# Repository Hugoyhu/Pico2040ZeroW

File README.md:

# Pico2040ZeroW
Raspberry Pi Form Factor, RP2040, Wireless support with ESP-01

2 Layer board, Rpi Form factor for pwr in, SD, pinout.

Optional ESP01 for wifi connectivity.

NOTE: THIS IS A NON-TESTED DESIGN. I HAVE NOT YET TRIED IT NOR REVIEWED WITH OTHERS. PLEASE KEEP THIS IN MIND WHEN TRYING TO BUILD ONE YOURSELF.

It is compatible with Python, (snek lang), C/C++, and Rust.

Schematic is modified off the Raspberry Pi foundation's reference schematic and carrier demo board schematics with modifications.

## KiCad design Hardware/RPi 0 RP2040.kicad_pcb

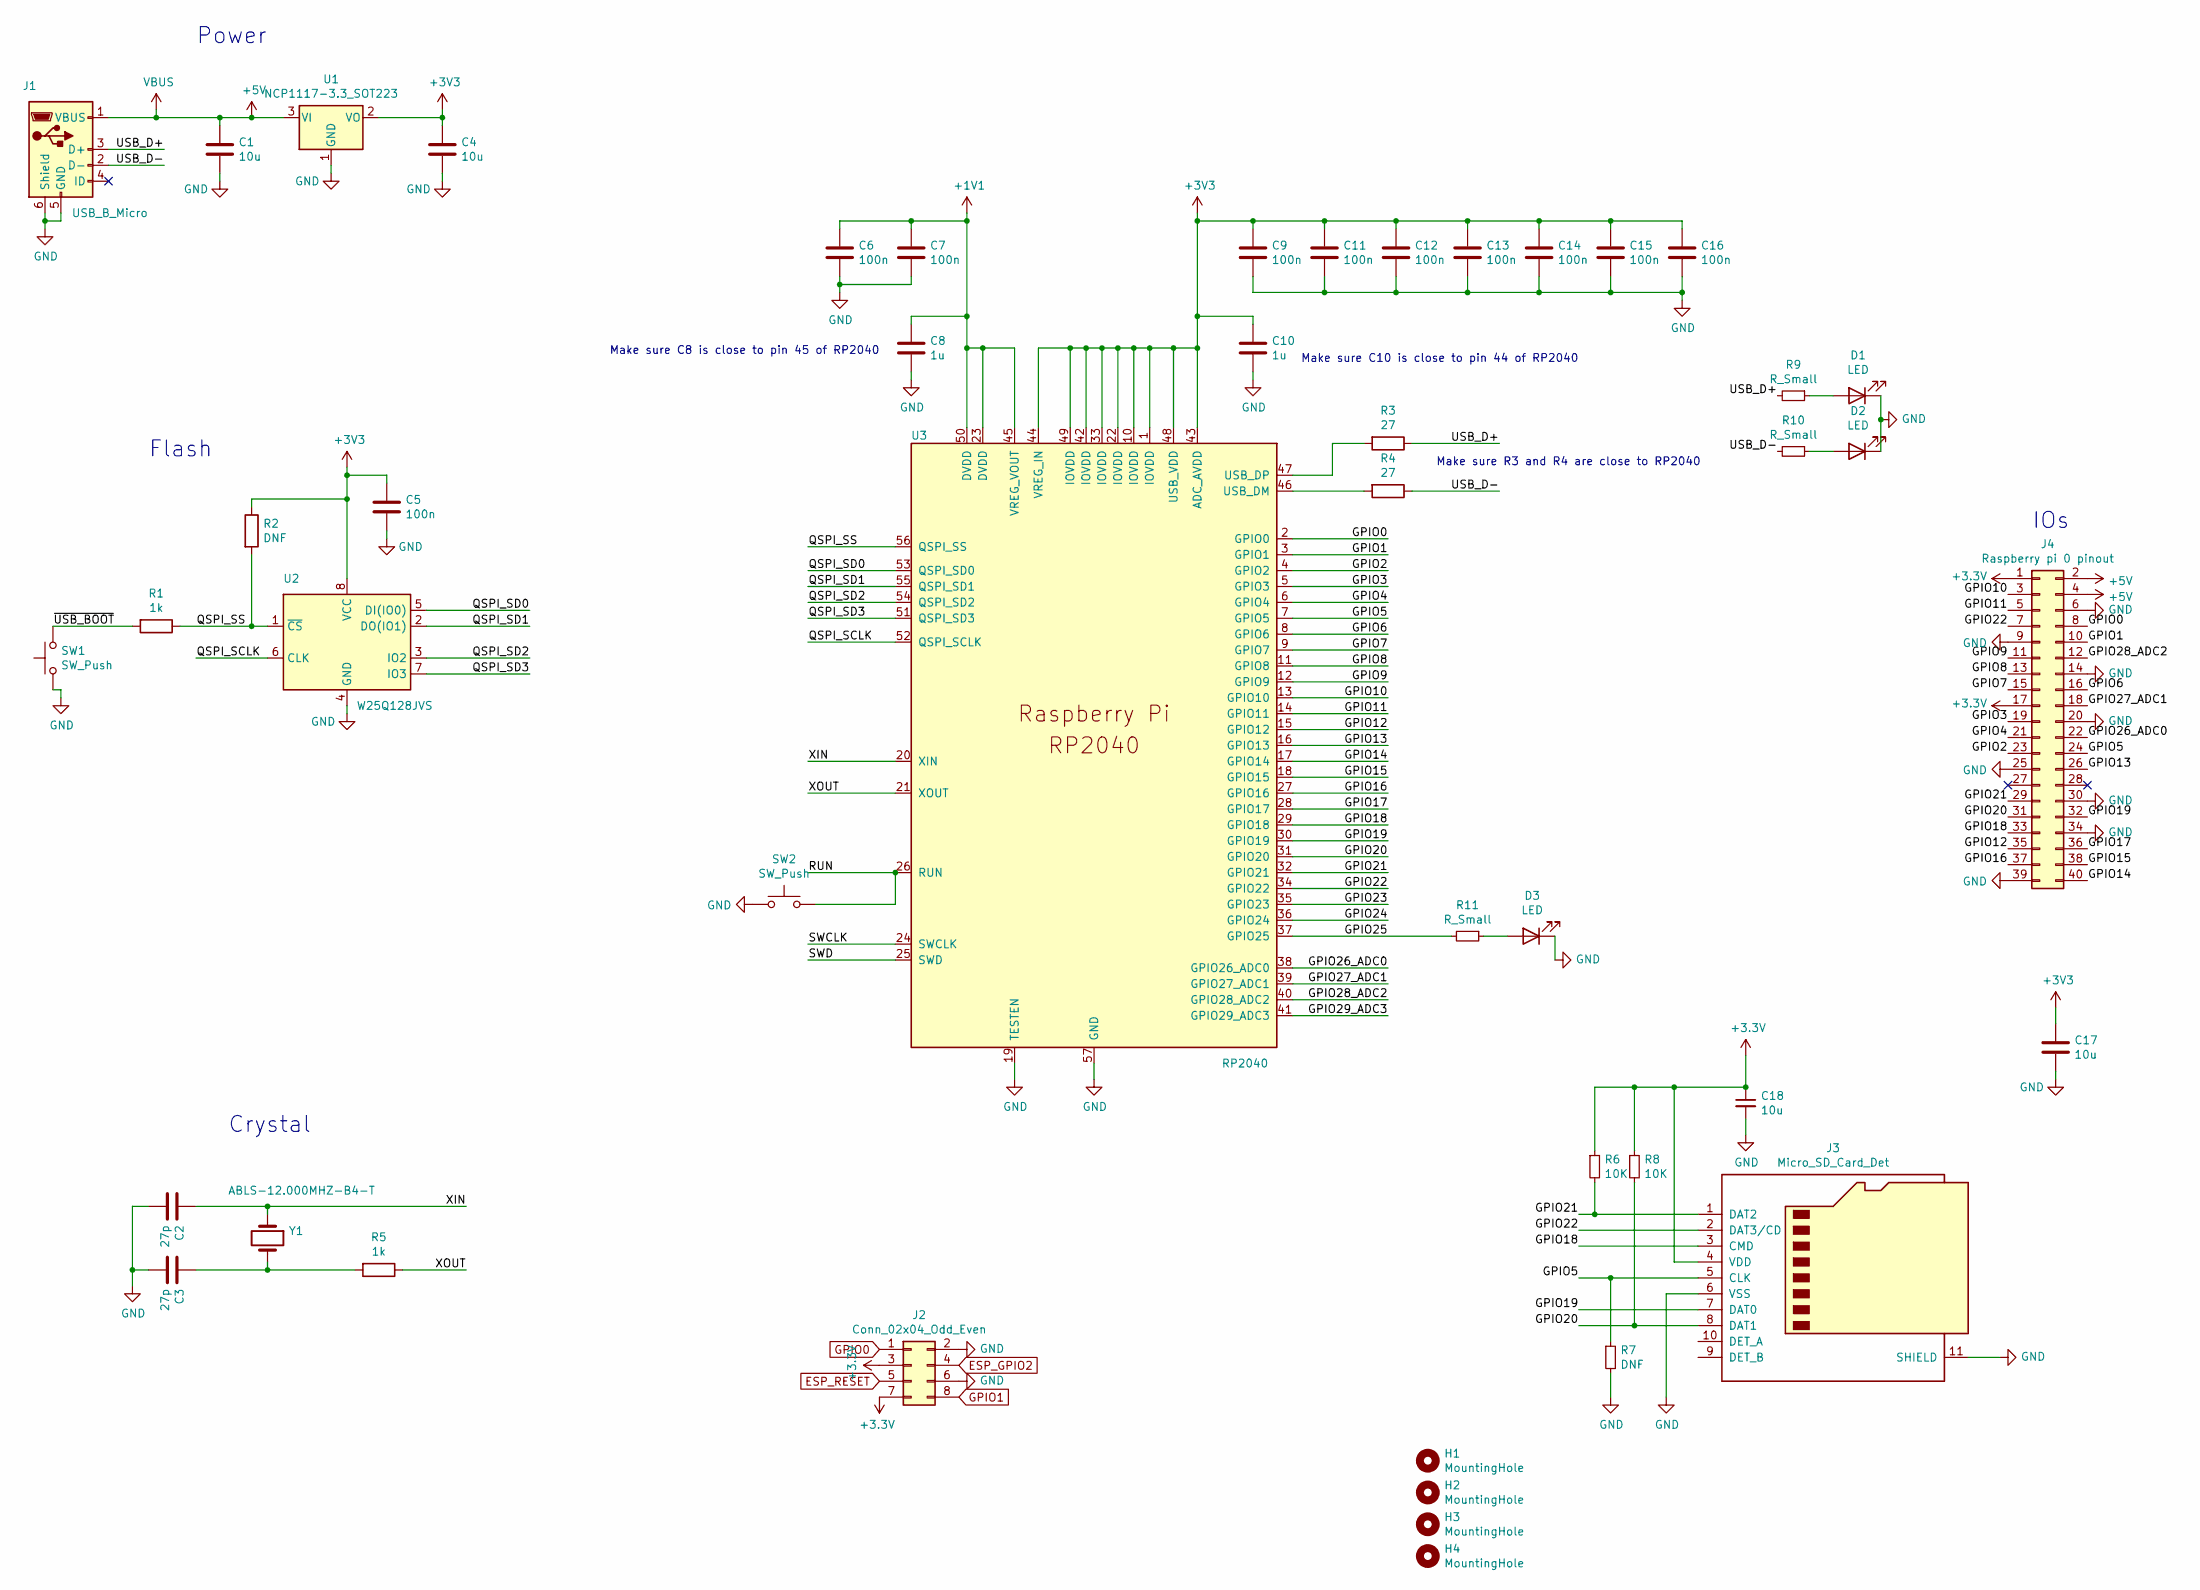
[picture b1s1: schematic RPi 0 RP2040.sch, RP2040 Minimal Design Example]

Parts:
C1, C4, C17, C18: 10u; C_0805_2012Metric_Pad1.18x1.45mm_HandSolder
C2, C3: 27p; C_0603_1608Metric_Pad1.08x0.95mm_HandSolder
C5, C6, C7, C9, C11, C12, C13, C14, C15, C16: 100n; C_0603_1608Metric_Pad1.08x0.95mm_HandSolder
C8, C10: 1u; C_0603_1608Metric_Pad1.08x0.95mm_HandSolder
D1, D2, D3: LED; LED_0603_1608Metric_Pad1.05x0.95mm_HandSolder
H1, H2, H3, H4: MountingHole; MountingHole_2.7mm_M2.5
J1: USB_B_Micro; USB_Micro-B_Amphenol_10103594-0001LF_Horizontal_modified
J2: Conn_02x04_Odd_Even; PinSocket_2x04_P2.54mm_Vertical
J3: Micro_SD_Card_Det; 104031-0811
J4: Raspberry pi 0 pinout; PinSocket_2x20_P2.54mm_Vertical
R1, R5: 1k; R_0603_1608Metric_Pad0.98x0.95mm_HandSolder
R2, R7: DNF; R_0603_1608Metric_Pad0.98x0.95mm_HandSolder
R3, R4: 27; R_0603_1608Metric_Pad0.98x0.95mm_HandSolder
R6, R8: 10K; R_0603_1608Metric_Pad0.98x0.95mm_HandSolder
R9, R10, R11: R_Small; R_0603_1608Metric_Pad0.98x0.95mm_HandSolder
SW1, SW2: SW_Push; Panasonic_EVQPUK_EVQPUB
U1: NCP1117-3.3_SOT223; SOT-223-3_TabPin2
U2: W25Q128JVS; SOIC-8_5.23x5.23mm_P1.27mm
U3: RP2040; RP2040-QFN-56
Y1: ABLS-12.000MHZ-B4-T; Crystal_SMD_HC49-US

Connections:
+1V1: C6.1, C7.1, C8.1, U3.23 (DVDD), U3.45 (VREG_VOUT), U3.50 (DVDD)
+5V: C1.1, J1.1 (VBUS), J4.2, J4.4, U1.3 (VI)
/GPIO2: J4.23, U3.4 (GPIO2)
/GPIO3: J4.19, U3.5 (GPIO3)
/GPIO4: J4.21, U3.6 (GPIO4)
/GPIO5: J3.5 (CLK), J4.24, R7.1, U3.7 (GPIO5)
/GPIO6: J4.16, U3.8 (GPIO6)
/GPIO7: J4.15, U3.9 (GPIO7)
/GPIO8: J4.13, U3.11 (GPIO8)
/GPIO9: J4.11, U3.12 (GPIO9)
/GPIO10: J4.3, U3.13 (GPIO10)
/GPIO11: J4.5, U3.14 (GPIO11)
/GPIO12: J4.35, U3.15 (GPIO12)
/GPIO13: J4.26, U3.16 (GPIO13)
/GPIO14: J4.40, U3.17 (GPIO14)
/GPIO15: J4.38, U3.18 (GPIO15)
/GPIO16: J4.37, U3.27 (GPIO16)
/GPIO17: J4.36, U3.28 (GPIO17)
/GPIO18: J3.3 (CMD), J4.33, U3.29 (GPIO18)
/GPIO19: J3.7 (DAT0), J4.32, U3.30 (GPIO19)
/GPIO20: J3.8 (DAT1), J4.31, R8.2, U3.31 (GPIO20)
/GPIO21: J3.1 (DAT2), J4.29, R6.2, U3.32 (GPIO21)
/GPIO22: J3.2 (DAT3/CD), J4.7, U3.34 (GPIO22)
/GPIO23: U3.35 (GPIO23)
/GPIO24: U3.36 (GPIO24)
/GPIO25: R11.2, U3.37 (GPIO25)
/GPIO26_ADC0: J4.22, U3.38 (GPIO26_ADC0)
/GPIO27_ADC1: J4.18, U3.39 (GPIO27_ADC1)
/GPIO28_ADC2: J4.12, U3.40 (GPIO28_ADC2)
/GPIO29_ADC3: U3.41 (GPIO29_ADC3)
/QSPI_SCLK: U2.6 (CLK), U3.52 (QSPI_SCLK)
/QSPI_SD0: U2.5 (DI(IO0)), U3.53 (QSPI_SD0)
/QSPI_SD1: U2.2 (DO(IO1)), U3.55 (QSPI_SD1)
/QSPI_SD2: U2.3 (IO2), U3.54 (QSPI_SD2)
/QSPI_SD3: U2.7 (IO3), U3.51 (QSPI_SD3)
/QSPI_SS: R1.1, R2.2, U2.1 (~CS), U3.56 (QSPI_SS)
/RUN: SW2.2, U3.26 (RUN)
/SWCLK: U3.24 (SWCLK)
/SWD: U3.25 (SWD)
/USB_D+: J1.3 (D+), R3.1, R9.2
/USB_D-: J1.2 (D-), R4.1, R10.2
/XIN: C2.1, U3.20 (XIN), Y1.1
/XOUT: R5.1, U3.21 (XOUT)
/~USB_BOOT: R1.2, SW1.2
ESP_GPIO2: J2.4
ESP_RESET: J2.5
GND: C1.2, C2.2, C3.2, C4.2, C5.2, C6.2, C7.2, C8.2, C9.2, C10.2, C11.2, C12.2, C13.2, C14.2, C15.2, C16.2, C17.2, C18.2, D1.1 (K), D2.1 (K), D3.1 (K), J1.5 (GND), J1.6 (Shield), J2.2, J2.6, J3.6 (VSS), J3.11 (SHIELD), J4.6, J4.9, J4.14, J4.20, J4.25, J4.30, J4.34, J4.39, R7.2, SW1.1, SW2.1, U1.1 (GND), U2.4 (GND), U3.19 (TESTEN), U3.57 (GND)
GPIO0: J2.1, J4.8, U3.2 (GPIO0)
GPIO1: J2.8, J4.10, U3.3 (GPIO1)
unnamed: C3.1, R5.2, Y1.2
unnamed: D1.2 (A), R9.1
unnamed: D2.2 (A), R10.1
unnamed: D3.2 (A), R11.1
unnamed: R3.2, U3.47 (USB_DP)
unnamed: R4.2, U3.46 (USB_DM)

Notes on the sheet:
Make sure C10 is close to pin 44 of RP2040
Make sure C8 is close to pin 45 of RP2040
Crystal
Flash
Power
IOs
Make sure R3 and R4 are close to RP2040

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
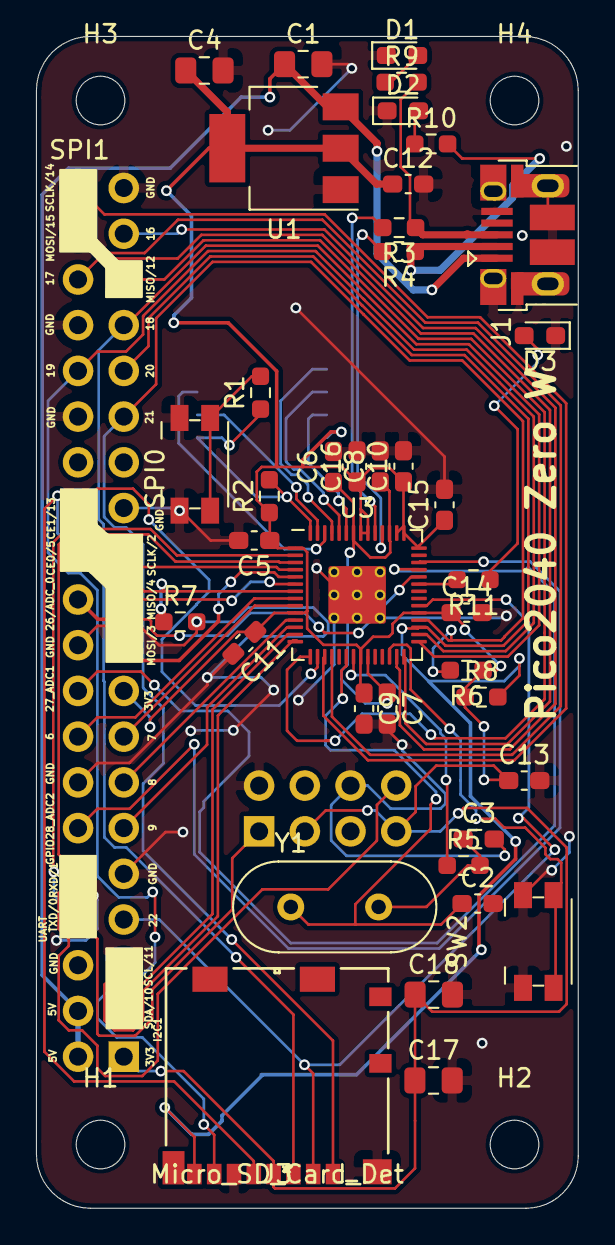
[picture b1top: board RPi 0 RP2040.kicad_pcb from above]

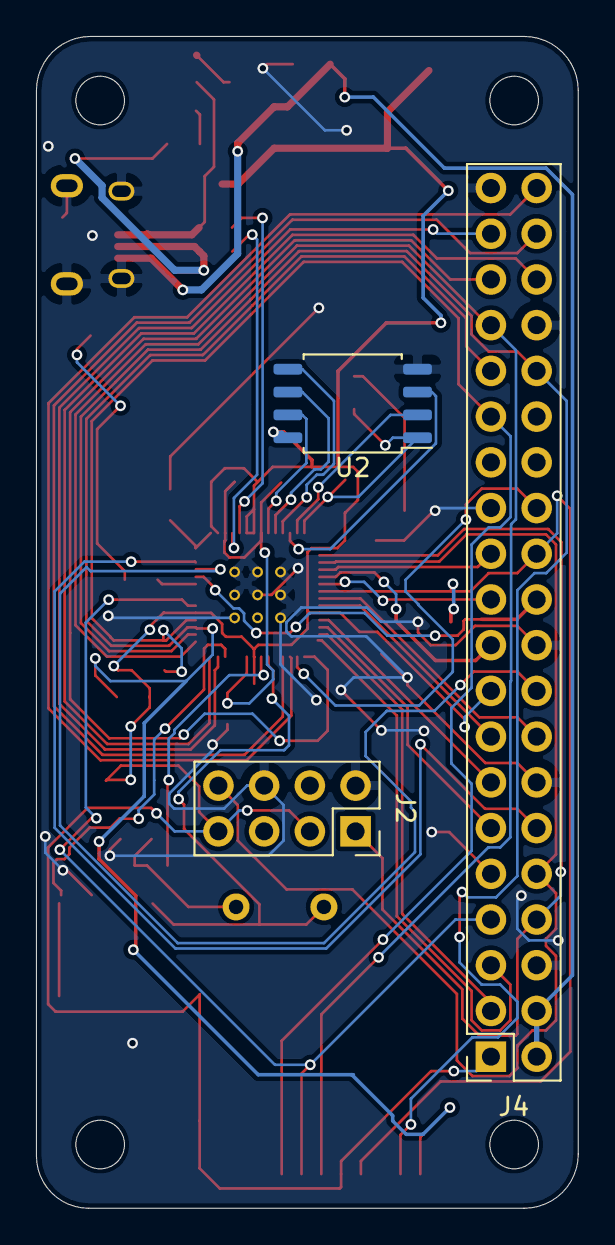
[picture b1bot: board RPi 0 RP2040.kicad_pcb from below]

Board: 2 copper layers, 30.1 x 65.1 mm, 46 parts (3 on the bottom side), 49 nets.

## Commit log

2021-02-10 Add hardware files
2021-02-12 Create v1.1 Folder and Info Txt file
2021-02-12 Add files via upload
    Add PCB design files
2021-02-12 Add files via upload
    Add images of PCB and Schematic
2021-02-12 Add Images of PCB + Schematic, rename
2021-02-12 Upload PCB Render
2021-02-12 [ImgBot] Optimize images
    *Total -- 1,136.21kb -> 454.97kb (59.96%)
    /Schematic Image.png -- 329.12kb -> 58.09kb (82.35%)
    /PCB Image.png -- 244.98kb -> 81.50kb (66.73%)
    /PCB Render Image.png -- 280.96kb -> 156.83kb (44.18%)
    /Screen Shot 2021-02-11 at 9.20.06 PM.png -- 281.16kb -> 158.55kb (43.61%)

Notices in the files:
parts and their libraries:
Copyright 2016 Accelerated Designs. All rights reserved.
